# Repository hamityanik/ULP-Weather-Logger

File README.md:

# ULP Weather Logger
Yet another ESP8266 (ESP-03) based ultra low power wi-fi weather logger with 4 sensors

 (@hamityanik)

> **Features**

> - Working with two **AA** battery
> - Ultra low power consumption
> - **4 sensors and 6 measurements:**
>  - HDC1080 - Temperature & Humidity
>  - LPS25HB - Pressure
>  - VEML6070 - Ultraviolet Index
>  - TSL2561 - Ambient & Infrared
> - Built-in 3.3v Boost Converter
> - TPL5111 System Timer (20 mins update interval, can be customized via resistors)
> - Battery voltage monitor
> - UART port for programming & debugging 

## Blynk Integration

## How can you buy one?

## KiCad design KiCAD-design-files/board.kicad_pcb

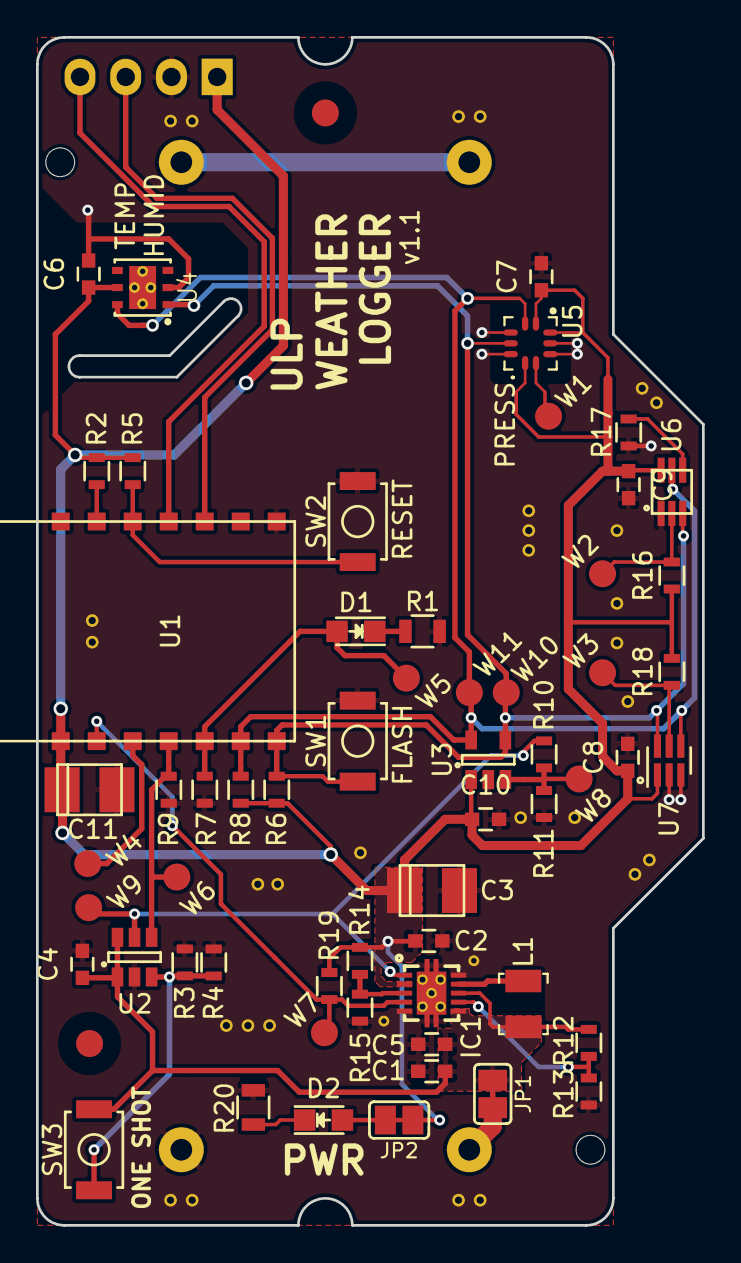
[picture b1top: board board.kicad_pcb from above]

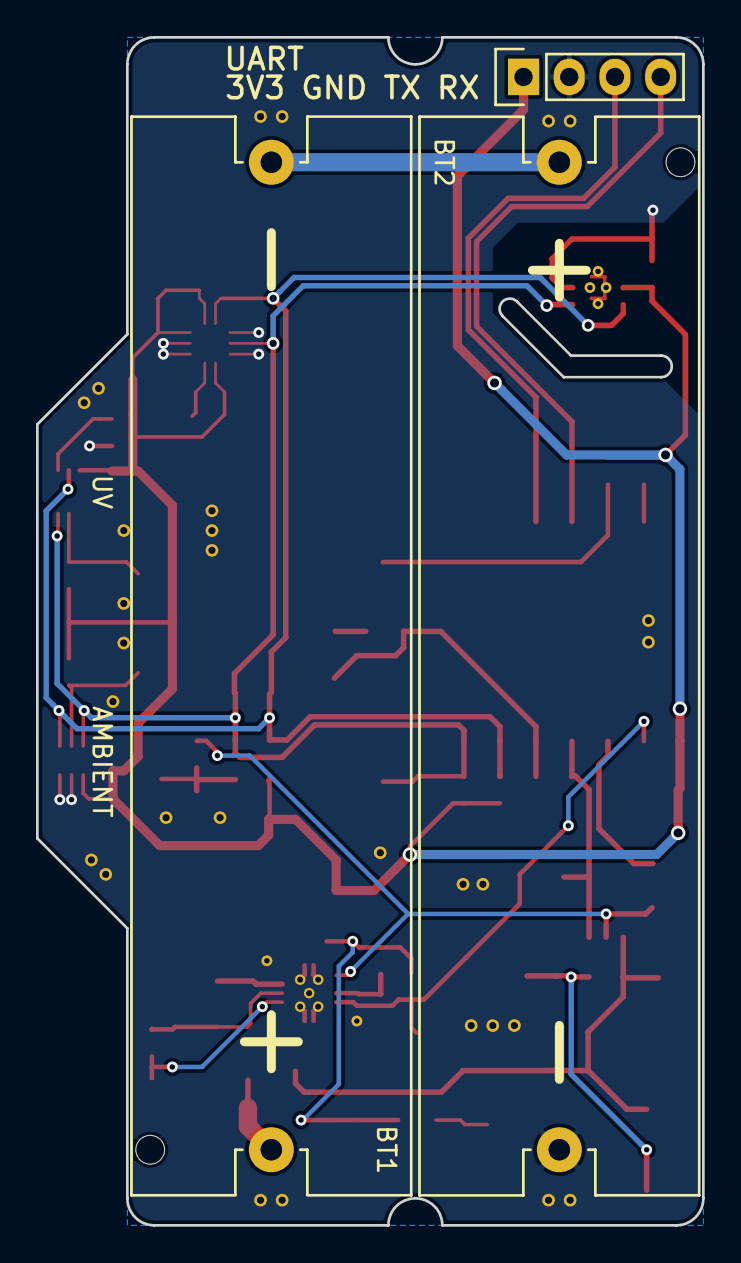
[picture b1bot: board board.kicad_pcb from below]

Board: 2 copper layers, 37.0 x 66.0 mm, 63 parts (3 on the bottom side), 26 nets.

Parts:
BT1, BT2: 1015; Keystone_1015_Holder_Battery_AA
C1: 10uF; C_0603
C2: 2.2uF; C_0603
C3: DNP; TantalC_SizeB_EIA-3528_Reflow
C4, C5, C6, C7, C8, C9, C10: 0.1uF; C_0603
C11: 100uF; TantalC_SizeB_EIA-3528_Reflow
D1: LTST-C170KFKT; LED_0805
D2: LTST-C171KRKT; LED_0805
FID1, FID2: FIDUCIAL; Fiducial
IC1: TPS61025; TI_DRC_S-PVSON-N10
JP1, JP2: JUMPER; SJ_OPEN
L1: 6.8uH; Inductor_1210
P1: CONN_01X04; Pin_Header_Straight_1x04
R1, R20: 1k; R_0805
R2, R13, R14: 0R; R_0603
R3: 140k; R_0603
R4: 174k; R_0603
R5, R6, R7, R8, R9, R16, R18: 10k; R_0603
R10: 1k; R_0603
R11: 390k; R_0603
R12, R15: DNP; R_0603
R17: 270k; R_0603
R19: 1M; R_0603
SW1, SW2, SW3: PTS820 J15M SMTR LFS; Tact_Switch_Top_PTS820
U1: ESP8266-ESP-03
U2: TPL5111; SOT-23-6
U3: MCP3021; SOT-23-5
U4: HDC1080; WSON-6-PAD
U5: LPS25HB; ST_LPS25HB
U6: VEML6070; OPLGA6
U7: TSL2561; WDFN-6_2x2mm_Pitch0.65mm
W1: PRES_INT; Measurement_Point_Round-SMD-Pad_Small
W2: UV_INT; Measurement_Point_Round-SMD-Pad_Small
W3: AMB_INT; Measurement_Point_Round-SMD-Pad_Small
W4: GPIO_12; Measurement_Point_Round-SMD-Pad_Small
W5: L; Measurement_Point_Round-SMD-Pad_Small
W6: DONE; Measurement_Point_Round-SMD-Pad_Small
W7: LOWBATT; Measurement_Point_Round-SMD-Pad_Small
W8: BATT_VOUT; Measurement_Point_Round-SMD-Pad_Small
W9: DRVn; Measurement_Point_Round-SMD-Pad_Small
W10: SDA; Measurement_Point_Round-SMD-Pad_Small
W11: SCL; Measurement_Point_Round-SMD-Pad_Small

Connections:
+3V3: C2.1, C3.1, C6.1, C7.1, C8.1, C9.1, C10.1, C11.1, D2.2, IC1.2, JP2.1, JP2.2, P1.1, R2.1, R5.1, R6.1, R8.1, R14.1, R16.1, R18.1, R19.1, U1.8, U3.1, U4.5, U5.1, U5.6, U5.10, U6.6, U7.1
+BATT: BT1.1, C1.1, C4.1, C5.1, IC1.6, IC1.8, JP1.1, JP1.2, L1.1, R12.1, SW3.1, U2.1, U2.6
/BATT_VOUT: R10.2, R11.1, U3.3, W8.1
/DONE: R9.1, U1.11, U2.4, W6.1
/DRVn: IC1.1, R10.1, U2.5, W9.1
/FB: IC1.3, R14.2, R15.1
/GPIO_12: U1.10, W4.1
/L: D1.2, R7.1, U1.12, W5.1
/LBI: IC1.7, R12.2, R13.1
/LOWBATT: IC1.4, R19.2, U1.9, W7.1
/M_DRV: R3.1, R4.1, SW3.2, U2.3
/RX: P1.4, U1.4
/SCL: R8.2, U1.13, U3.5, U4.6, U5.2, U6.5, U7.4, W11.1
/SDA: R6.2, SW1.1, U1.14, U3.4, U4.1, U5.4, U6.3, U7.6, W10.1
/TX: P1.3, U1.3
GND: BT2.2, C1.2, C2.2, C3.2, C4.2, C5.2, C6.2, C7.2, C8.2, C9.2, C10.2, C11.2, IC1.0, IC1.5, IC1.10, P1.2, R1.2, R3.2, R4.2, R7.2, R9.2, R11.2, R13.2, R15.2, R17.1, R20.2, SW1.2, SW2.2, U1.1, U2.2, U3.2, U4.2, U5.3, U5.5, U5.8, U5.9, U6.1, U7.2, U7.3
unnamed: BT1.2, BT2.1
unnamed: D1.1, R1.1
unnamed: D2.1, R20.1
unnamed: IC1.9, L1.2
unnamed: R2.2, U1.6
unnamed: R5.2, SW2.1, U1.5
unnamed: R16.2, U6.2, W2.1
unnamed: R17.2, U6.4
unnamed: R18.2, U7.5, W3.1
unnamed: U5.7, W1.1

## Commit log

2017-01-17 Photo added.
2017-03-21 Some improvements during first manufacturing
2017-03-21 R3 and R4 selection table added
2017-03-21 Lines to be customised
2017-03-21 Resistor selection table updated
2017-03-24 GIFs added
2017-04-05 Power consumption measurement images added
2017-04-09 Manual update gif added.
2017-04-23 Some improvements & 3D CAD files added
2017-04-23 Gerber files updated
2017-04-23 Some images added
2017-04-23 Deleted old gerber files
2017-05-17 Arduino IDE Config menu for programming added
